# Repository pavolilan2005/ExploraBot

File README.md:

# ExploraBot
ExploraBot_V1 es una placa orientada al control y sensado de un robot explorador autónomo o teleoperado. Su arquitectura central gira en torno a un microcontrolador ESP32, integrando etapas de potencia para motores de corriente directa, acondicionamiento de energía, y una suite completa de sensores para navegación y localización espacial.

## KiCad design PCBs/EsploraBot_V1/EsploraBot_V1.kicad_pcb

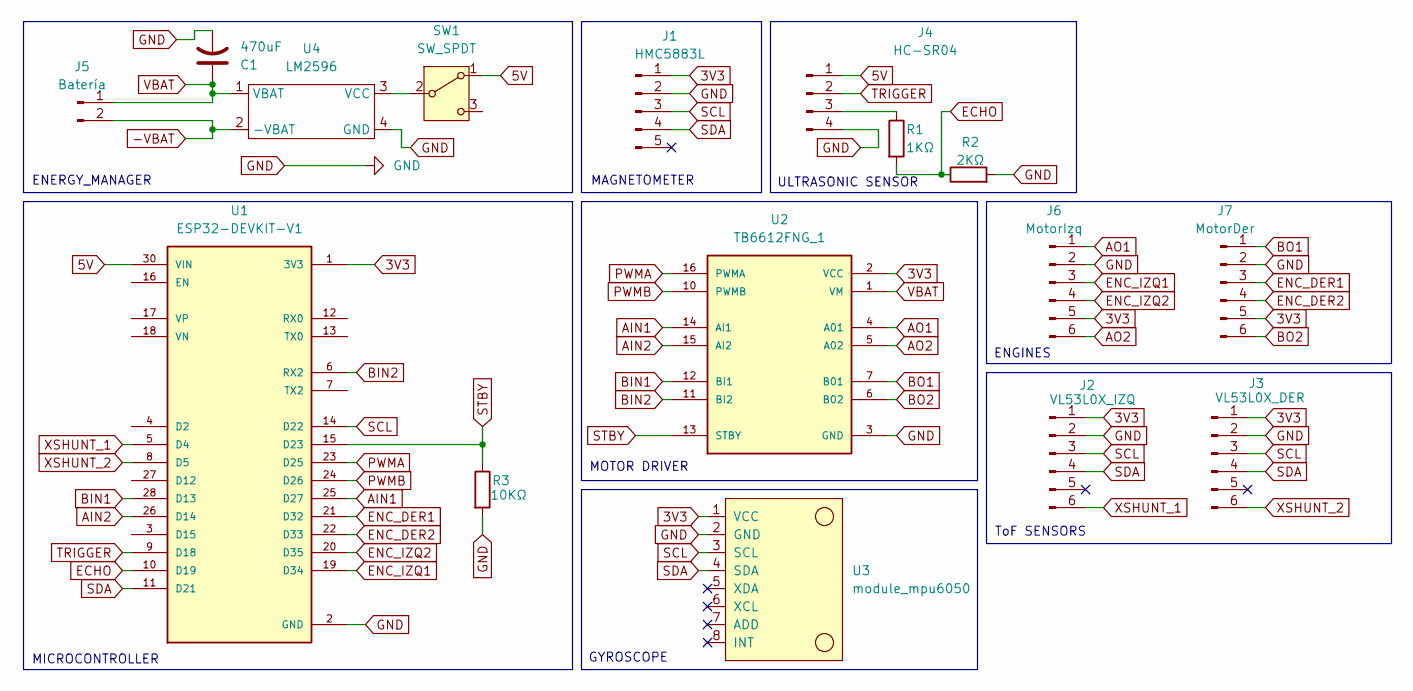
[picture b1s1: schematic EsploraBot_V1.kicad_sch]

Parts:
C1: 470uF; CP_Radial_D6.3mm_P2.50mm
J1: HMC5883L; PinHeader_1x05_P2.54mm_Vertical
J2: VL53L0X_IZQ; PinSocket_1x06_P2.54mm_Vertical
J3: VL53L0X_DER; PinSocket_1x06_P2.54mm_Vertical
J4: HC-SR04; PinSocket_1x04_P2.54mm_Vertical
J5: Batería; TerminalBlock_Phoenix_MKDS-1,5-2_1x02_P5.00mm_Horizontal
J6: MotorIzq; TerminalBlock_Phoenix_MKDS-1,5-6_1x06_P5.00mm_Horizontal
J7: MotorDer; TerminalBlock_Phoenix_MKDS-1,5-6_1x06_P5.00mm_Horizontal
R1: 1KΩ; R_Axial_DIN0204_L3.6mm_D1.6mm_P7.62mm_Horizontal
R2: 2KΩ; R_Axial_DIN0204_L3.6mm_D1.6mm_P7.62mm_Horizontal
R3: 10KΩ; R_Axial_DIN0204_L3.6mm_D1.6mm_P7.62mm_Horizontal
SW1: SW_SPDT; PinSocket_1x03_P2.54mm_Vertical
U1: ESP32-DEVKIT-V1; MODULE_ESP32_DEVKIT_V1; PARTREV N/A
U2: TB6612FNG_1; tb6612fng; PARTREV 11-13-17
U3: module_mpu6050
U4: LM2596; Buck Module

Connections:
3V3: J1.1, J2.1, J3.1, J6.5, J7.5, U1.1 (3V3), U2.2 (VCC), U3.1 (VCC)
5V: J4.1, SW1.1 (A), U1.30 (VIN)
-VBAT: J5.2, U4.2 (-VBAT)
AIN1: U1.25 (D27), U2.14 (AI1)
AIN2: U1.26 (D14), U2.15 (AI2)
AO1: J6.1, U2.4 (A01)
AO2: J6.6, U2.5 (A02)
BIN1: U1.28 (D13), U2.12 (BI1)
BIN2: U1.6 (RX2), U2.11 (BI2)
BO1: J7.1, U2.7 (B01)
BO2: J7.6, U2.6 (B02)
ECHO: R1.2, R2.1, U1.10 (D19)
ENC_DER1: J7.3, U1.21 (D32)
ENC_DER2: J7.4, U1.22 (D33)
ENC_IZQ1: J6.3, U1.19 (D34)
ENC_IZQ2: J6.4, U1.20 (D35)
GND: C1.2, J1.2, J2.2, J3.2, J4.4, J6.2, J7.2, R2.2, R3.2, U1.2 (GND), U1.29 (GND), U2.3 (GND), U2.8 (GND), U2.9 (GND), U3.2 (GND), U4.4 (GND)
unnamed: J4.3, R1.1
unnamed: SW1.2 (B), U4.3 (VCC)
PWMA: U1.23 (D25), U2.16 (PWMA)
PWMB: U1.24 (D26), U2.10 (PWMB)
SCL: J1.3, J2.3, J3.3, U1.14 (D22), U3.3 (SCL)
SDA: J1.4, J2.4, J3.4, U1.11 (D21), U3.4 (SDA)
STBY: R3.1, U1.15 (D23), U2.13 (STBY)
TRIGGER: J4.2, U1.9 (D18)
VBAT: C1.1, J5.1, U2.1 (VM), U4.1 (VBAT)
XSHUNT_1: J2.6, U1.5 (D4)
XSHUNT_2: J3.6, U1.8 (D5)

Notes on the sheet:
ULTRASONIC SENSOR
MICROCONTROLLER
GYROSCOPE
ENERGY_MANAGER
ToF SENSORS
ENGINES
MOTOR DRIVER
MAGNETOMETER

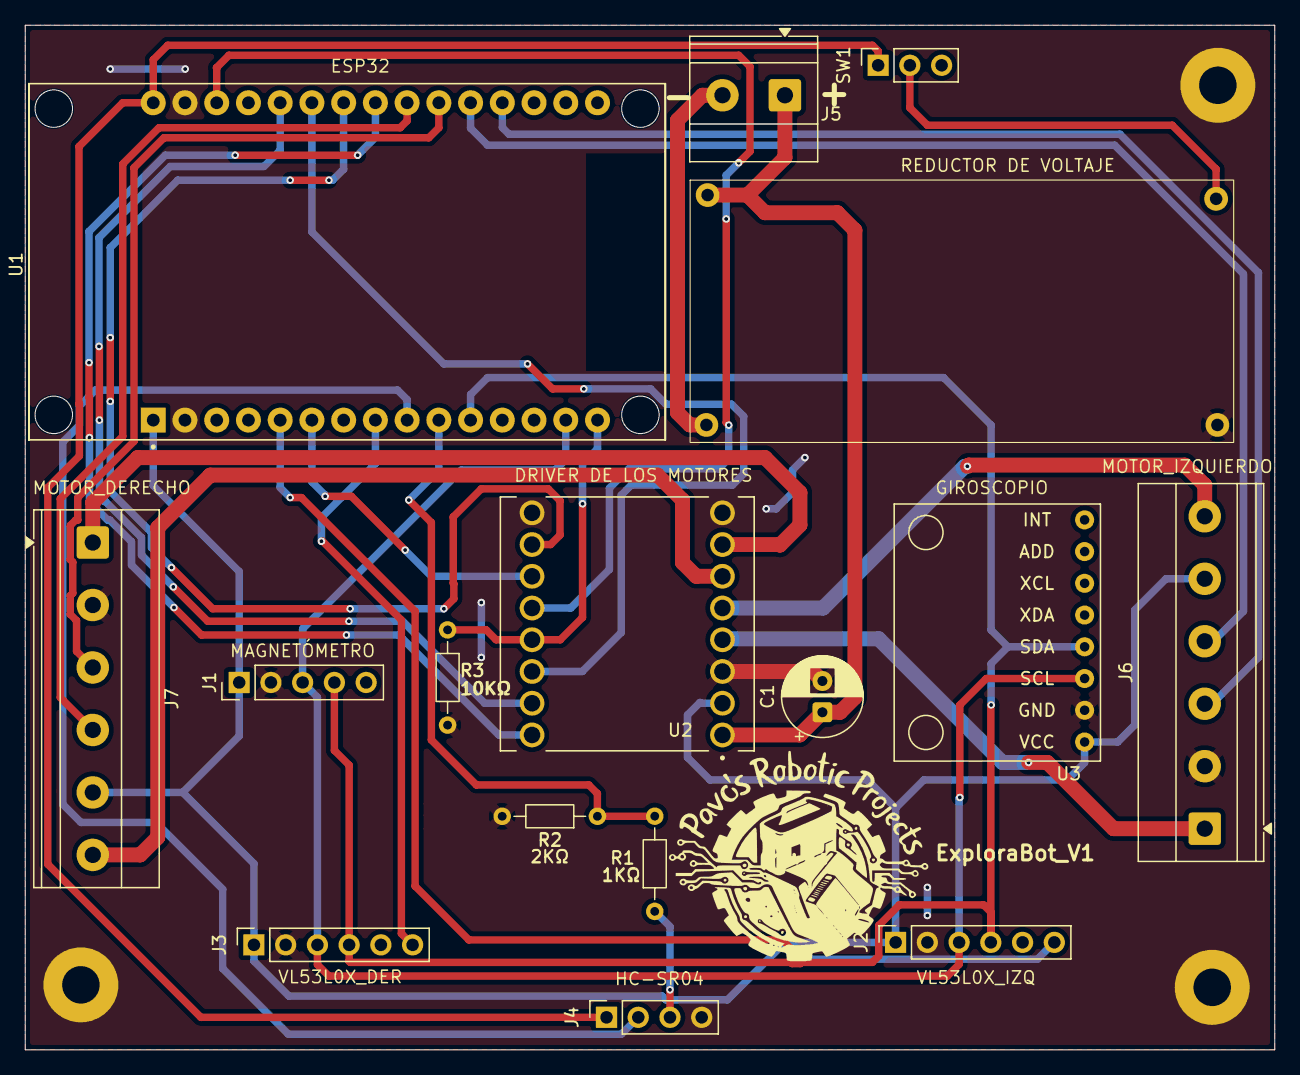
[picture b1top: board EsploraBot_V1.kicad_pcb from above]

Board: 2 copper layers, 100.0 x 82.0 mm, 16 parts (0 on the bottom side), 28 nets.
